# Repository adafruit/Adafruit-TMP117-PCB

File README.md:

## Adafruit TMP117 High-accuracy Temperature Sensor PCB

<a href="http://www.adafruit.com/products/4821"><br/>
Click here to purchase one from the Adafruit shop</a>

PCB files for the Adafruit TMP117 High-accuracy Temperature Sensor. 

Format is EagleCAD schematic and board layout
* https://www.adafruit.com/product/4821

### Description

The TMP117 Precision Temperature Sensor is an I2C temperature sensor that will help you easily add temperature measurement and adjustment to your project. In addition to the obvious support for reading the temperature, the TMP117 can also monitor the temperature and alert you when corrective action needs to be taken. 

With 16-bit measurement resolution and ±0.1°C accuracy, as well as high and low temperature alerts and interrupt support, and hardware support required for NIST traceability, this temperature sensor is perfect for applications where you need to keep a close eye on temperature. The manufacturer, Texas Instruments even suggest it for use in sensitive applications like thermostats and cold chain asset tracking or even gas and heat meters!

To make using it as easy as possible, we’ve put the TMP117 on a breakout PCB  in our Stemma QT form factor with a sprinkle of support circuitry to give you options when testing. You can either use a bread board or the Stemma QT connectors, and it is compatible with 5V voltage levels as commonly found on Arduinos as well as 3.3V logic used by many other boards like the Raspberry Pi or our Feathers. To get started, all you need to do is look over the Pinouts page for familiarize yourself with the board, and then use the Arduino or Python & CircuitPython pages for instructions on how to wire up the TMP117 to your board, as well as libraries and example code to get you started.

### License

Adafruit invests time and resources providing this open source design, please support Adafruit and open-source hardware by purchasing products from [Adafruit](https://www.adafruit.com)!

Designed by Limor Fried/Ladyada for Adafruit Industries.

Creative Commons Attribution/Share-Alike, all text above must be included in any redistribution. 
See license.txt for additional details.

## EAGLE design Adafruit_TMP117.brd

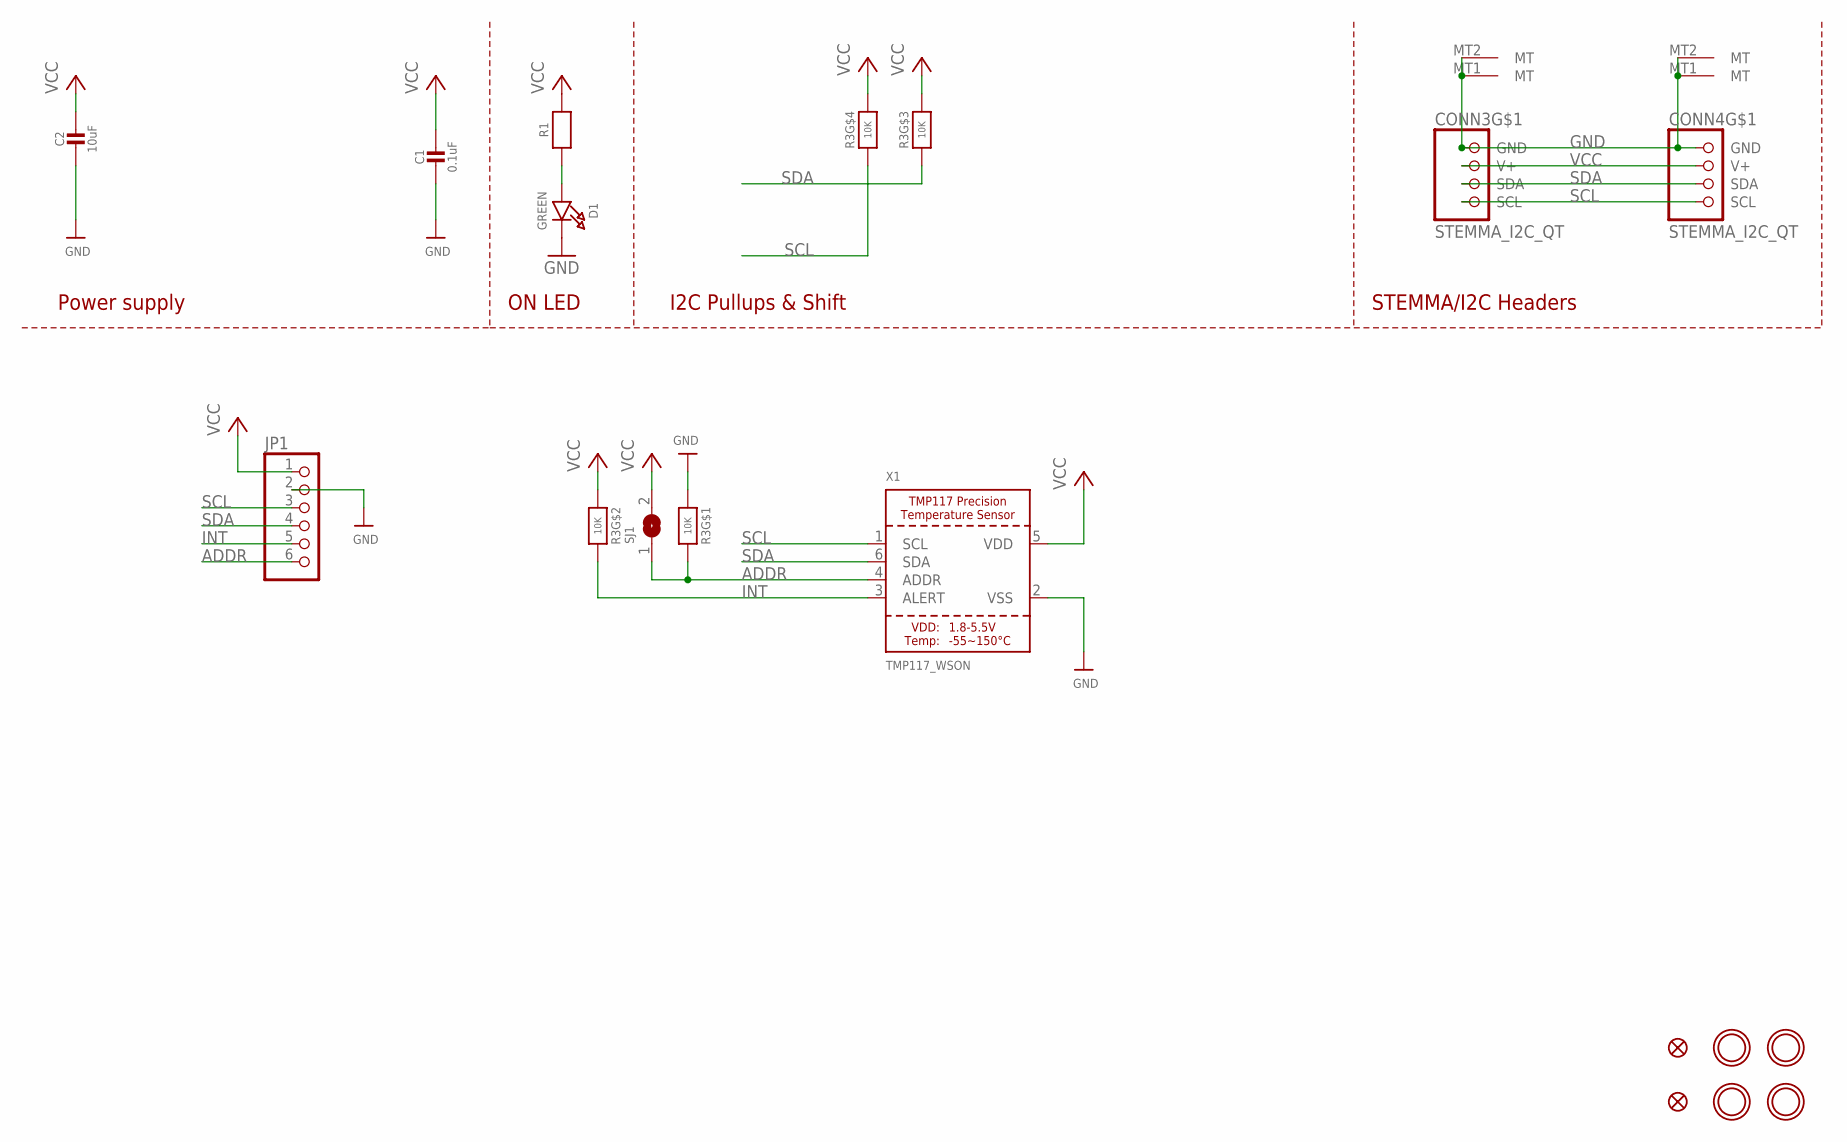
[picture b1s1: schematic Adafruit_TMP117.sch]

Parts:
C1: 0.1uF; 0603-NO
C2: 10uF; 0805-NO
CONN3, CONN4: STEMMA_I2C_QT; JST_SH4
D1: GREEN; CHIPLED_0603_NOOUTLINE
FID3, FID4: FIDUCIAL_1MM
JP1: HEADER-1X670MIL; 1X06_ROUND_70
R1: RESISTOR_0603_NOOUT; 0603-NO
R3: 10K; RESPACK_4X0603
SJ1: SOLDERJUMPER; SOLDERJUMPER_ARROW_NOPASTE
U$1, U$17, U$19, U$21: MOUNTINGHOLE2.5; MOUNTINGHOLE_2.5_PLATED
X1: TMP117_WSON; WSON-6

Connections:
ADDR: JP1.6, R3.8 (2), SJ1.1, X1.4 (ADDR)
GND: C1.2, C2.2, CONN3.1 (GND), CONN3.MT1 (MT), CONN3.MT2 (MT), CONN4.1 (GND), CONN4.MT1 (MT), CONN4.MT2 (MT), D1.C, JP1.2, R3.1, X1.2 (VSS)
INT: JP1.5, R3.7 (2), X1.3 (ALERT)
unnamed: D1.A, R1.1
SCL: CONN3.4 (SCL), CONN4.4 (SCL), JP1.3, R3.4 (1), X1.1 (SCL)
SDA: CONN3.3 (SDA), CONN4.3 (SDA), JP1.4, R3.3 (1), X1.6 (SDA)
VCC: C1.1, C2.1, CONN3.2 (V+), CONN4.2 (V+), JP1.1, R1.2, R3.2 (1), R3.5 (2), R3.6 (2), SJ1.2, X1.5 (VDD)

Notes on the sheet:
I2C Pullups & Shift
STEMMA/I2C Headers
ON LED
Power supply

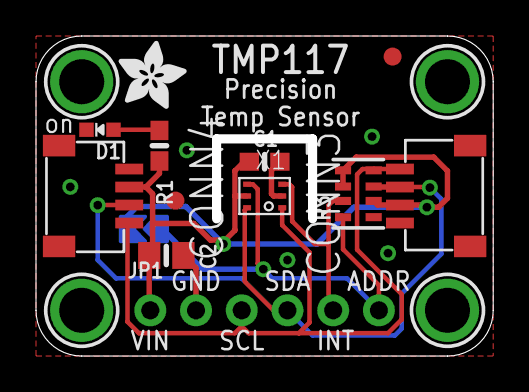
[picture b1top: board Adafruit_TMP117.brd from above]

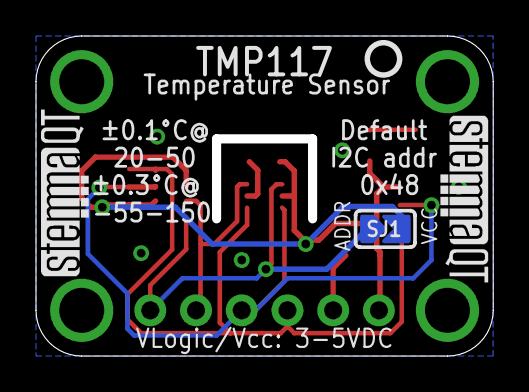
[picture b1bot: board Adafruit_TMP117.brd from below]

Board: 2 copper layers, 25.4 x 17.8 mm, 20 parts (4 on the bottom side), 7 nets.

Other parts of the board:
U$22: ADAFRUIT_3.5MM
U$25: PCBFEAT-REV-040
U$30, U$31: STEMMAQT

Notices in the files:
parts and their libraries:
microbuilder: This work is placed in the public domain, and may be freely used for commercial and non-commercial work with the following conditions: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
